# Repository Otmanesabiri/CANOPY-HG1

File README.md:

# Canopy GH-1 — Autonomous Greenhouse Controller

**Canopy GH-1** is an open-hardware, industrial-grade greenhouse climate and irrigation controller powered by the **Raspberry Pi Compute Module 4 (CM4)**. It pairs a deterministic fail-safe control loop and hardware safety interlocks with an embedded **Claude AI agronomic assistant** accessible via web dashboard, REST API, and local voice interface.

---

## Repository Structure

```text
canopy/
├── hw/                         # Custom 4-layer carrier PCB (150 x 100 mm)
│   ├── design.py               # Single-source-of-truth component & netlist DB (186 parts, 162 nets)
│   ├── build_sch.py            # Programmatic KiCad 7/8 schematic generator
│   ├── build_pcb.py            # Programmatic KiCad 7/8 PCB placement & outline generator
│   ├── check_net.py            # Schematic-to-design netlist consistency verifier
│   ├── route_prep.py           # Netclass config & Specctra DSN export for autorouting
│   ├── post_route.py           # SES import, 4-layer copper zone pour, DRC & Gerber/BOM/POS export
│   ├── kicad/                  # KiCad project (canopy.kicad_sch, canopy.kicad_pcb, canopy.dsn, canopy.ses)
│   └── fab/                    # Manufacturing outputs (Gerbers, Excellon drills, BOM, pick-and-place)
├── software/                   # Python 3.11+ asynchronous control daemon & web UI
│   ├── canopy/
│   │   ├── __main__.py         # CLI entry point & daemon runner
│   │   ├── engine.py           # Main async event loop, watchdog heartbeat & subsystem orchestrator
│   │   ├── control.py          # Hysteresis climate, VPD, CO2, lighting & irrigation controller + interlocks
│   │   ├── hal.py              # Hardware abstraction layer (I2C/1-Wire/GPIO drivers + physics simulator)
│   │   ├── radios.py           # LoRa RFM95W sub-GHz telemetry radio driver
│   │   ├── voice.py            # Dual I2S MEMS mic & MAX98357A speaker voice assistant pipeline
│   │   ├── agent.py            # Anthropic Claude tool-calling assistant with setpoint guardrails
│   │   ├── store.py            # SQLite time-series telemetry & event logger
│   │   └── webapp.py           # aiohttp REST API & real-time dark-mode dashboard
│   └── tests/
│       └── test_canopy.py      # 19 unit, safety interlock, 48h simulation & AI tool-calling tests
├── os/                         # Embedded Raspberry Pi OS Bookworm (arm64) customization
│   ├── build-image.sh          # Automated loop-device OS image builder
│   ├── BUILD.md                # Reproducible Docker container build instructions
│   ├── config.txt.append       # Boot config (I2C, SPI, I2S, 1-Wire, hardware watchdog)
│   ├── overlays/               # Device Tree overlay (canopy-gh1-overlay.dts & compiled canopy-gh1.dtbo)
│   └── systemd/                # canopy.service (with WatchdogSec=30s) & canopy-firstboot.service
├── enclosure/                  # Weatherproof 3D-printable enclosure (IP65 gasketed design)
│   ├── canopy_enclosure.scad   # Parametric OpenSCAD source (body, lid, DIN clip, lightpipes)
│   ├── canopy_base.stl         # Enclosure base mesh (and .3mf)
│   └── canopy_lid.stl          # Enclosure lid mesh (and .3mf)
└── docs/                       # Detailed subsystem documentation
    ├── hardware.md             # Schematic, power tree, and PCB layout architecture
    ├── software.md             # Control loop, safety interlocks, and REST API reference
    ├── os-image.md             # OS image build and first-boot provisioning guide
    └── assembly.md             # Mechanical assembly and field wiring instructions
```

---

## Key Features

### 1. Hardware (`canopy/hw`)
- **Compute:** Raspberry Pi Compute Module 4 (CM4) via dual 100-pin Hirose `DF40C-100DS-0.4V` mezzanine connectors.
- **Dual Redundant Power:**
  - **USB-C PD 20V @ 3A (60W)** via `STUSB4500QTR` autonomous USB-PD sink controller (`U1`).
  - **12–24V DC Field Terminal** (`J4`) with ideal-diode/Schottky OR-ing.
  - **High-Efficiency Buck Stages:** `LMR33640ADDAR` (5V @ 4A) + `AP62250WU-7` (3.3V @ 2.5A).
- **Actuation & Switching:**
  - **4x SPDT High-Power Relays (`K1`–`K4`):** Roof vents, exhaust fan, circulation fan, and heater (`ULN2803ADWR` sink driver with `V_FIELD` flyback suppression).
  - **4x 24V Irrigation Solenoid Outputs (`J8`):** Independent zone control with status LEDs.
  - **2x 0–10V / PWM Dimming Outputs:** Supplemental grow lights and variable-speed EC fans.
- **Sensing & Connectivity:**
  - **I2C1 (`J5`):** `SHT31` temperature/humidity, `SCD41` photoacoustic CO2, `PCF8523` RTC with CR1220 backup (`BT1`), and `ADS1115` 16-bit ADC (`U9` — 2x capacitive soil moisture + 2x 0–10V analog inputs with `BAT54S` clamping).
  - **1-Wire (`J6`):** Multi-probe `DS18B20` soil/water temperature sensing.
  - **LoRa Radio (`U6`):** `RFM95W` 868/915 MHz SPI transceiver with u.FL/SMA antenna port (`J10`).
  - **Audio I/O:** Dual `ICS-43434` I2S MEMS microphones (`MK1`, `MK2`) + `MAX98357A` 3.2W Class-D speaker amp (`U7`).
  - **Networking & USB:** Gigabit Ethernet RJ45 with integrated magnetics (`J3`) + dual USB 2.0 Type-A ports (`J2` via `USB2514B-AEZC`).

### 2. Control Software & Safety Engine (`canopy/software`)
- **Deterministic Closed-Loop Control:** Runs independently of cloud connectivity or AI availability.
- **Hardware-Enforced Safety Interlocks:**
  - **Heater / Ventilation Mutual Exclusion:** Never energizes the heater while roof vents or exhaust fans are active.
  - **Thermal Emergency Cutoffs:** Force-off heater above `35 °C`, emergency full ventilation above `40 °C`, emergency frost heating below `5 °C`.
  - **Runaway Irrigation Cutoff:** Hard maximum continuous open time per solenoid valve.
- **Claude AI Assistant Integration:**
  - Supports natural-language diagnostics and guarded setpoint adjustments (`get_status`, `get_history`, `set_target`, `pulse_irrigation`, `set_override`) with strict physical safety boundaries.

---

## Quick Start

### 1. Run the Software Test Suite & Simulator
```powershell
python -m venv .venv
.venv\Scripts\Activate.ps1

pip install -e canopy/software pytest pytest-asyncio pytest-aiohttp tzdata

# Execute all 19 unit, safety interlock & 48h simulation tests
pytest canopy/software/tests/test_canopy.py -v
```

### 2. Launch the Live Simulation Daemon & Web UI
```powershell
python -m canopy --config canopy/os/rootfs/etc/canopy/config.yaml --sim
```
Open **`http://localhost:8080`** in your browser to view the live dashboard, sensor charts, actuator states, and Claude chat interface.

### 3. Hardware Verification & PCB Autorouting Pipeline (Docker)
```powershell
# 1. Verify 100% netlist match between design.py and KiCad schematic
python canopy/hw/check_net.py

# 2. Export Specctra DSN from KiCad 8
docker run --rm -v "${PWD}/canopy:/canopy" kicad/kicad:8.0 python3 /canopy/hw/route_prep.py

# 3. Run headless Freerouting to generate Specctra SES
docker run --rm -v "${PWD}/canopy:/canopy" eclipse-temurin:21-jre `
  java -jar /canopy/hw/lib/freerouting.jar `
  -de /canopy/hw/kicad/canopy.dsn `
  -do /canopy/hw/kicad/canopy.ses `
  --gui.enabled=false --router.max_passes=5

# 4. Import SES, pour 4-layer copper zones, run DRC & export Gerbers/BOM/POS
docker run --rm -v "${PWD}/canopy:/canopy" kicad/kicad:8.0 python3 /canopy/hw/post_route.py --fab
```

### 4. Compile Device Tree Overlay
```powershell
docker run --rm -v "${PWD}/canopy:/canopy" alpine:3.20 sh -c `
  "apk add --no-cache dtc && dtc -@ -I dts -O dtb -o /canopy/os/overlays/canopy-gh1.dtbo /canopy/os/overlays/canopy-gh1-overlay.dts"
```

---

## Verification Status

- **Software Tests:** `19 passed` (`test_canopy.py`) covering hysteresis, safety interlocks, 48-hour physics simulation, REST API, and Claude tool calls.
- **Hardware Netlist:** `186 components`, `162 nets`, `0 mismatches` between `design.py` and `canopy.kicad_sch`.
- **PCB Autorouting:** 5-pass headless Freerouting completed with `0 connection errors` (`canopy.ses`).
- **Device Tree Overlay:** `canopy-gh1.dtbo` compiled cleanly (`1,850 bytes`, 0 warnings).
- **Mechanical Fit:** 150 x 100 mm PCB and 143 x 93 mm M3 mounting hole pattern verified against `canopy_enclosure.scad`.
=======
# Canopy GH-1 greenhouse controller: work in progress (stopped early)

**This package is incomplete. The PCB is placed but NOT routed, and no OS image was built.**

| Item | Where | State |
|---|---|---|
| Design database (parts, MPNs, pin-to-net map) | `hw/design.py` | done; analog values and MPNs are from memory and need datasheet and stock checks |
| Schematic (KiCad 7) + PDF | `hw/kicad/`, `hw/canopy-schematic.pdf` | generated; KiCad's netlist matches the database (186 parts, 162 nets) |
| PCB | `hw/kicad/canopy.kicad_pcb` | placement, outline and planes only. **No tracks**: the autorouter was stopped at pass 8 of 25 with no result |
| Gerbers, drill, pick-and-place, BOM | `hw/fab_UNROUTED_do_not_manufacture/` | exported from the unrouted board. BOM and placement are fine for review; the Gerbers must not be sent to a fab |
| DRC report | `hw/drc_report.txt` | unrouted board: 499 unconnected pads, 359 violations (not yet triaged) |
| Enclosure | `enclosure/` (SCAD, STL, 3MF) | done; meshes watertight; never printed or ingress-tested |
| Software | `software/` | done; 19 tests pass; runs end to end in simulation. Real drivers, voice and the live Claude API call are untested |
| OS image | `os/` | build script, overlay, boot config and units only. The script was never run and nothing was booted |
| Docs | `docs/` | hardware, software, OS image, assembly |

Deviations from the brief: Raspberry Pi CM4 carrier instead of a soldered-down SoC (reasons in `docs/hardware.md`);
Zigbee through an internal USB port for a coordinator stick, not an on-board radio. `docs/hardware.md` section 7
describes the intended layout, not a finished one.

To continue: `cd hw && python3 route_prep.py`, run Freerouting on `kicad/canopy.dsn` to get `kicad/canopy.ses`,
then `python3 post_route.py --fab`. After that, USB and Ethernet pairs and the high-current power path still need
hand rework in KiCad before fabrication. Build the image with `os/build-image.sh` on a Debian/Ubuntu host.

Try the software: `cd software && pip install -e ".[dev]" && pytest`, then `python -m canopy -c cfg.yaml`
with `hardware: {mode: sim}` in the YAML.

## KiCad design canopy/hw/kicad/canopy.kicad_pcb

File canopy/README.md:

# Canopy GH-1 greenhouse controller: work in progress (stopped early)

**This package is incomplete. The PCB is placed but NOT routed, and no OS image was built.**

| Item | Where | State |
|---|---|---|
| Design database (parts, MPNs, pin-to-net map) | `hw/design.py` | done; analog values and MPNs are from memory and need datasheet and stock checks |
| Schematic (KiCad 7) + PDF | `hw/kicad/`, `hw/canopy-schematic.pdf` | generated; KiCad's netlist matches the database (186 parts, 162 nets) |
| PCB | `hw/kicad/canopy.kicad_pcb` | placement, outline and planes only. **No tracks**: the autorouter was stopped at pass 8 of 25 with no result |
| Gerbers, drill, pick-and-place, BOM | `hw/fab_UNROUTED_do_not_manufacture/` | exported from the unrouted board. BOM and placement are fine for review; the Gerbers must not be sent to a fab |
| DRC report | `hw/drc_report.txt` | unrouted board: 499 unconnected pads, 359 violations (not yet triaged) |
| Enclosure | `enclosure/` (SCAD, STL, 3MF) | done; meshes watertight; never printed or ingress-tested |
| Software | `software/` | done; 19 tests pass; runs end to end in simulation. Real drivers, voice and the live Claude API call are untested |
| OS image | `os/` | build script, overlay, boot config and units only. The script was never run and nothing was booted |
| Docs | `docs/` | hardware, software, OS image, assembly |

Deviations from the brief: Raspberry Pi CM4 carrier instead of a soldered-down SoC (reasons in `docs/hardware.md`);
Zigbee through an internal USB port for a coordinator stick, not an on-board radio. `docs/hardware.md` section 7
describes the intended layout, not a finished one.

To continue: `cd hw && python3 route_prep.py`, run Freerouting on `kicad/canopy.dsn` to get `kicad/canopy.ses`,
then `python3 post_route.py --fab`. After that, USB and Ethernet pairs and the high-current power path still need
hand rework in KiCad before fabrication. Build the image with `os/build-image.sh` on a Debian/Ubuntu host.

Try the software: `cd software && pip install -e ".[dev]" && pytest`, then `python -m canopy -c cfg.yaml`
with `hardware: {mode: sim}` in the YAML.

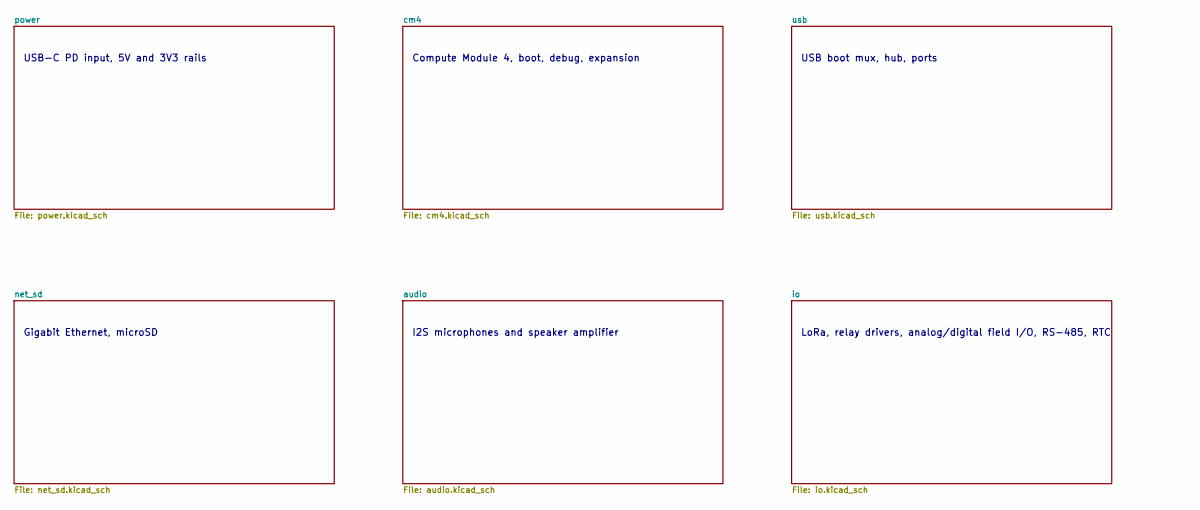
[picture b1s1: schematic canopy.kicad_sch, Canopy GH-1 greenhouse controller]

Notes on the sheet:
USB-C PD input, 5V and 3V3 rails
Compute Module 4, boot, debug, expansion
USB boot mux, hub, ports
Gigabit Ethernet, microSD
I2S microphones and speaker amplifier
LoRa, relay drivers, analog/digital field I/O, RS-485, RTC

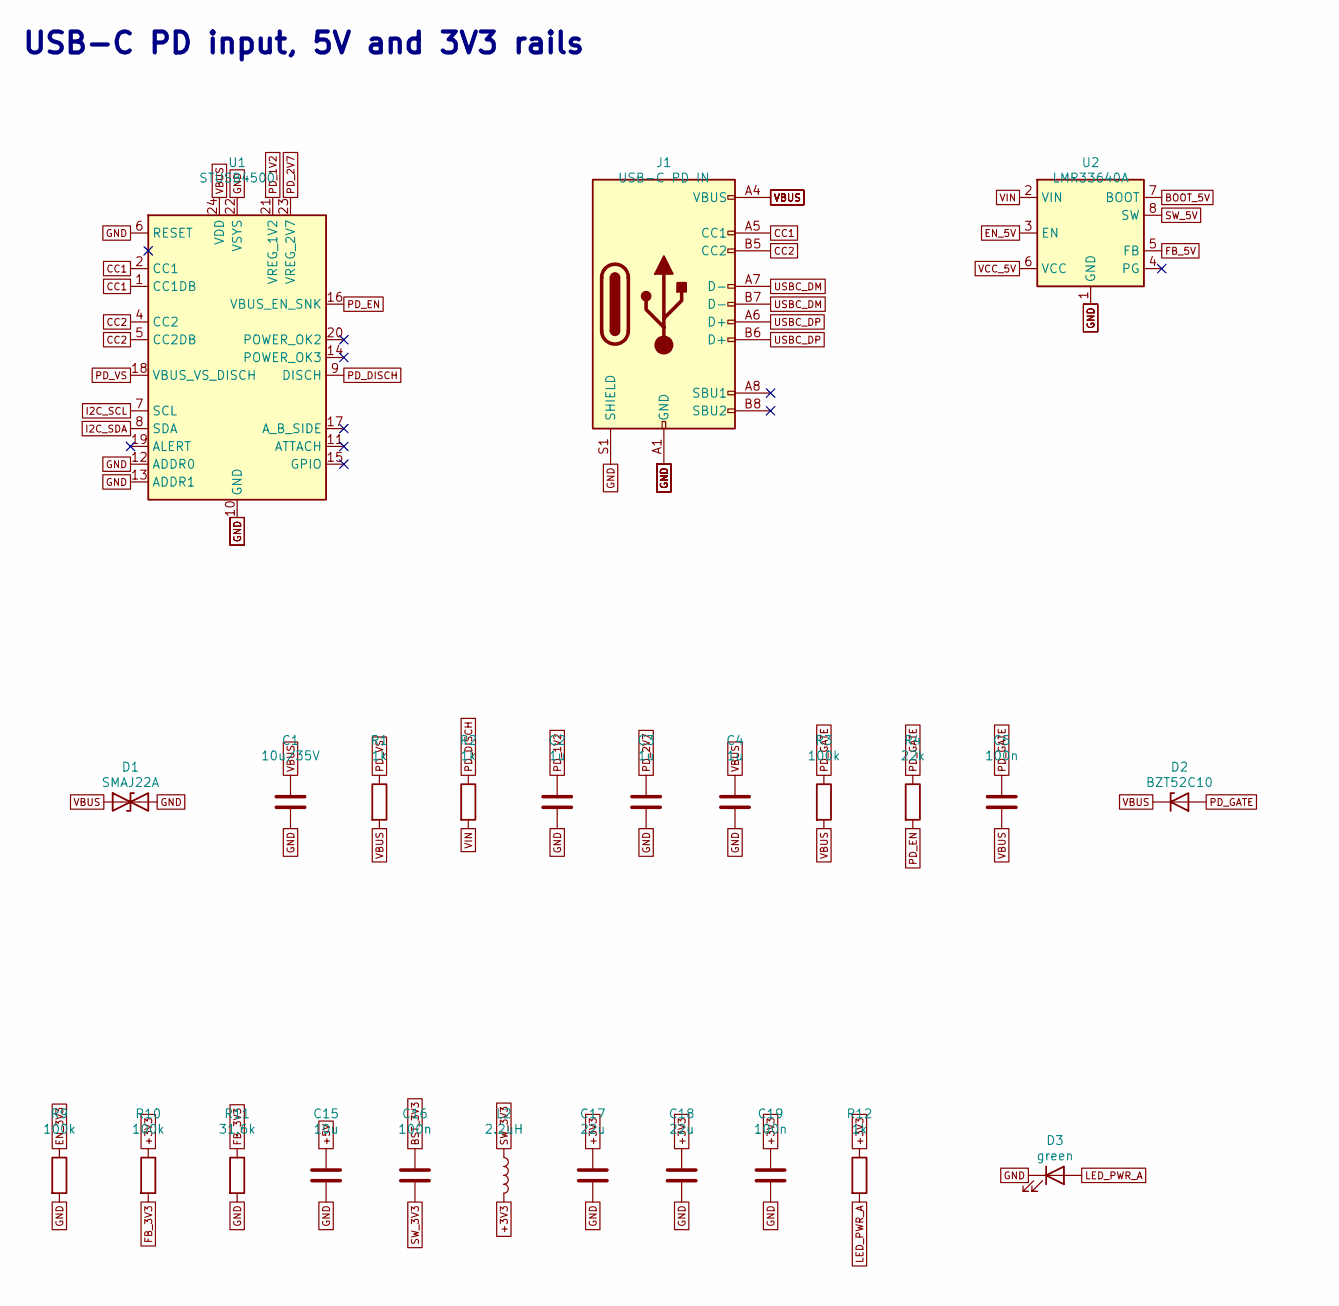
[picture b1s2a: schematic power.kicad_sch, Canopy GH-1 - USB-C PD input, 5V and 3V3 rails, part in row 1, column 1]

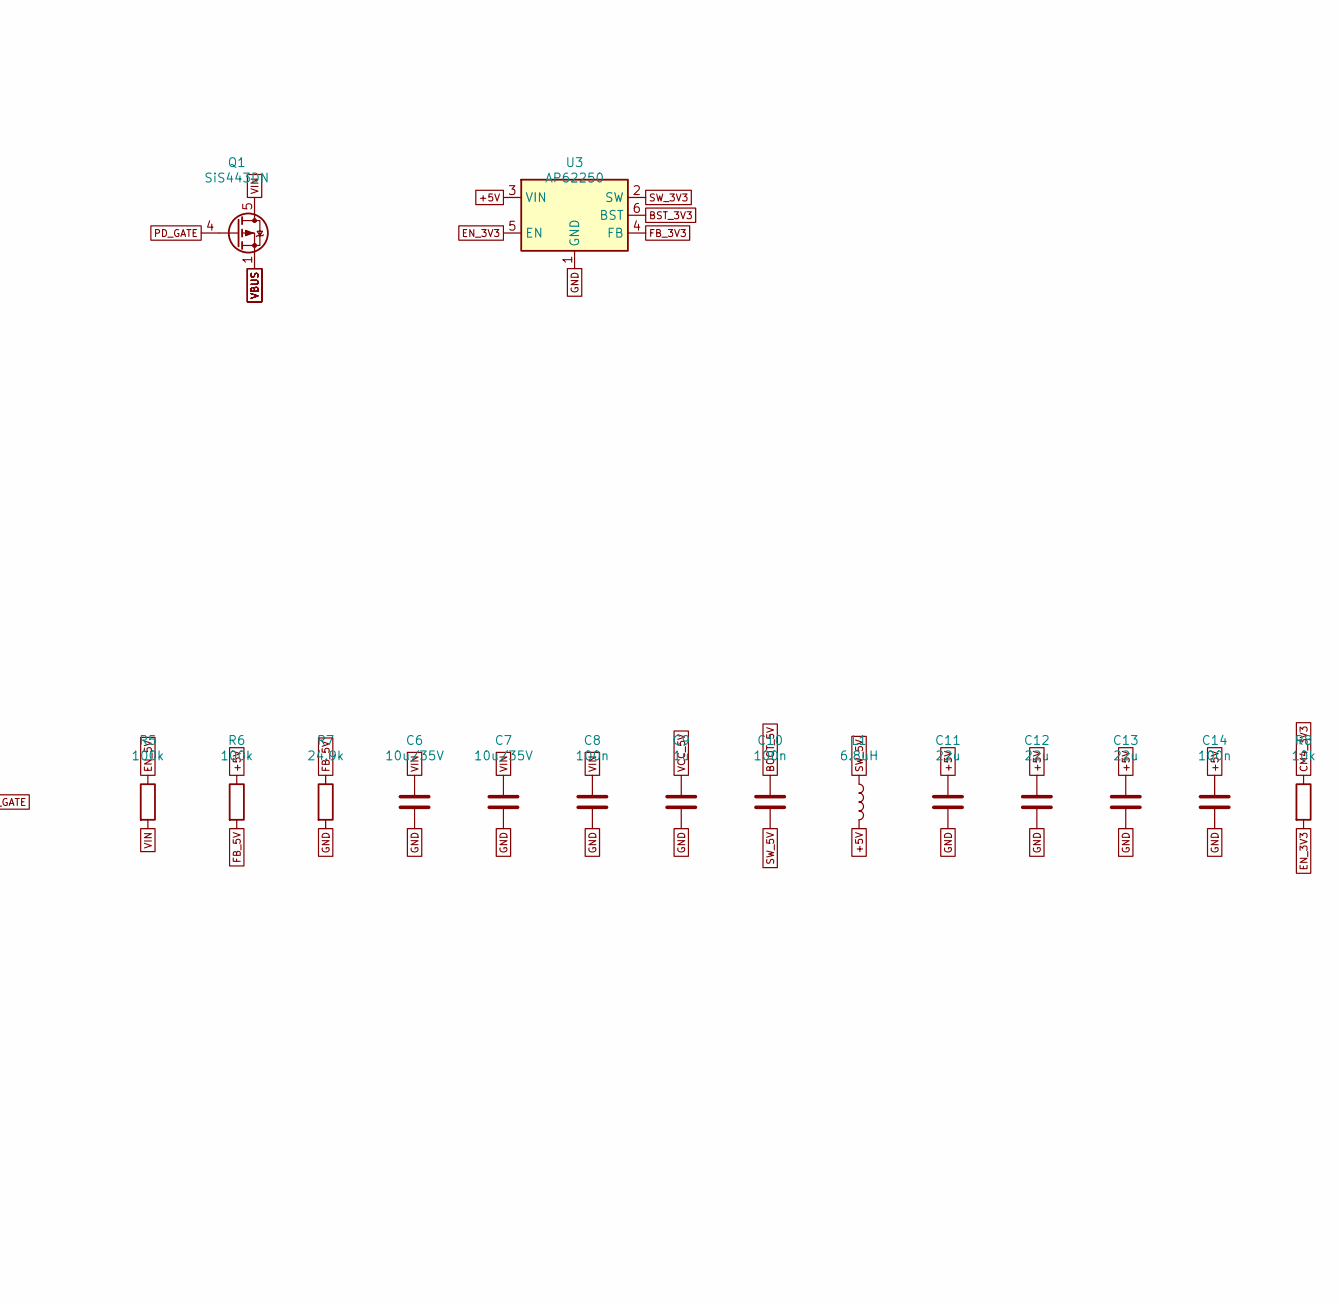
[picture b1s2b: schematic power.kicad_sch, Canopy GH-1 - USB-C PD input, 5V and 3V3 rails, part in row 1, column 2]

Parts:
C1, C6, C7: 10u/35V; C_1206_3216Metric; MPN GRM31CR6YA106KA12L
C2, C3, C4, C9: 1u; C_0603_1608Metric; MPN CL10A105KB8NNNC
C5, C8, C10, C14, C16, C19: 100n; C_0603_1608Metric; MPN GRM188R71H104KA93D
C11, C12, C13, C17, C18: 22u; C_0805_2012Metric; MPN GRM21BR61A226ME44L
C15: 10u; C_0603_1608Metric; MPN GRM188R61A106KE69D
D1: SMAJ22A; D_SMA; MPN SMAJ22A
D2: BZT52C10; D_SOD-123; MPN BZT52C10-7-F
D3: green; LED_0603_1608Metric; MPN LTST-C191KGKT
J1: USB-C PD IN; USB_C_Receptacle_GCT_USB4105-xx-A_16P_TopMnt_Horizontal; MPN USB4105-GF-A
L1: 6.8uH; L_Bourns_SRP7028A_7.3x6.6mm; MPN SRP7028A-6R8M
L2: 2.2uH; L_Coilcraft_XAL4020-XXX; MPN XAL4020-222MEC
Q1: SiS443DN; Vishay_PowerPAK_1212-8_Single; MPN SIS443DN-T1-GE3
R1, R2, R12: 1k; R_0603_1608Metric; MPN RC0603FR-071KL
R3, R5, R6, R9, R10: 100k; R_0603_1608Metric; MPN RC0603FR-07100KL
R4: 22k; R_0603_1608Metric; MPN RC0603FR-0722KL
R7: 24.9k; R_0603_1608Metric; MPN RC0603FR-0724K9L
R8: 10k; R_0603_1608Metric; MPN RC0603FR-0710KL
R11: 31.6k; R_0603_1608Metric; MPN RC0603FR-0731K6L
U1: STUSB4500; QFN-24-1EP_4x4mm_P0.5mm_EP2.7x2.7mm; MPN STUSB4500QTR
U2: LMR33640A; Texas_HSOP-8-1EP_3.9x4.9mm_P1.27mm_ThermalVias; MPN LMR33640ADDAR
U3: AP62250; TSOT-23-6; MPN AP62250WU-7

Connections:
+3V3: C17.1, C18.1, C19.1, L2.2, R10.1, R12.1; also elsewhere on the board
+5V: C11.1, C12.1, C13.1, C14.1, C15.1, L1.2, R6.1, U3.3 (VIN); also elsewhere on the board
BOOT_5V: C10.1, U2.7 (BOOT)
BST_3V3: C16.1, U3.6 (BST)
CC1: J1.A5 (CC1), U1.1 (CC1DB), U1.2 (CC1)
CC2: J1.B5 (CC2), U1.4 (CC2), U1.5 (CC2DB)
CM4_3V3: R8.1; also elsewhere on the board
EN_3V3: R8.2, R9.1, U3.5 (EN)
EN_5V: R5.1, U2.3 (EN)
FB_3V3: R10.2, R11.1, U3.4 (FB)
FB_5V: R6.2, R7.1, U2.5 (FB)
GND: C1.2, C2.2, C3.2, C4.2, C6.2, C7.2, C8.2, C9.2, C11.2, C12.2, C13.2, C14.2, C15.2, C17.2, C18.2, C19.2, D1.2 (A2), D3.1 (K), J1.A1 (GND), J1.A12 (GND), J1.B1 (GND), J1.B12 (GND), J1.S1 (SHIELD), R7.2, R9.2, R11.2, U1.6 (RESET), U1.10 (GND), U1.12 (ADDR0), U1.13 (ADDR1), U1.22 (VSYS), U1.25 (GND), U2.1 (GND), U2.9 (GND), U3.1 (GND); also elsewhere on the board
I2C_SCL: U1.7 (SCL); also elsewhere on the board
I2C_SDA: U1.8 (SDA); also elsewhere on the board
LED_PWR_A: D3.2 (A), R12.2
PD_1V2: C2.1, U1.21 (VREG_1V2)
PD_2V7: C3.1, U1.23 (VREG_2V7)
PD_DISCH: R2.1, U1.9 (DISCH)
PD_EN: R4.2, U1.16 (VBUS_EN_SNK)
PD_GATE: C5.1, D2.2 (A), Q1.4 (G), R3.1, R4.1
PD_VS: R1.1, U1.18 (VBUS_VS_DISCH)
SW_3V3: C16.2, L2.1, U3.2 (SW)
SW_5V: C10.2, L1.1, U2.8 (SW)
USBC_DM: J1.A7 (D-), J1.B7 (D-); also elsewhere on the board
USBC_DP: J1.A6 (D+), J1.B6 (D+); also elsewhere on the board
VBUS: C1.1, C4.1, C5.2, D1.1 (A1), D2.1 (K), J1.A4 (VBUS), J1.A9 (VBUS), J1.B4 (VBUS), J1.B9 (VBUS), Q1.1 (S), Q1.2 (S), Q1.3 (S), R1.2, R3.2, U1.24 (VDD)
VCC_5V: C9.1, U2.6 (VCC)
VIN: C6.1, C7.1, C8.1, Q1.5 (D), R2.2, R5.2, U2.2 (VIN)

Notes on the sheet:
USB-C PD input, 5V and 3V3 rails

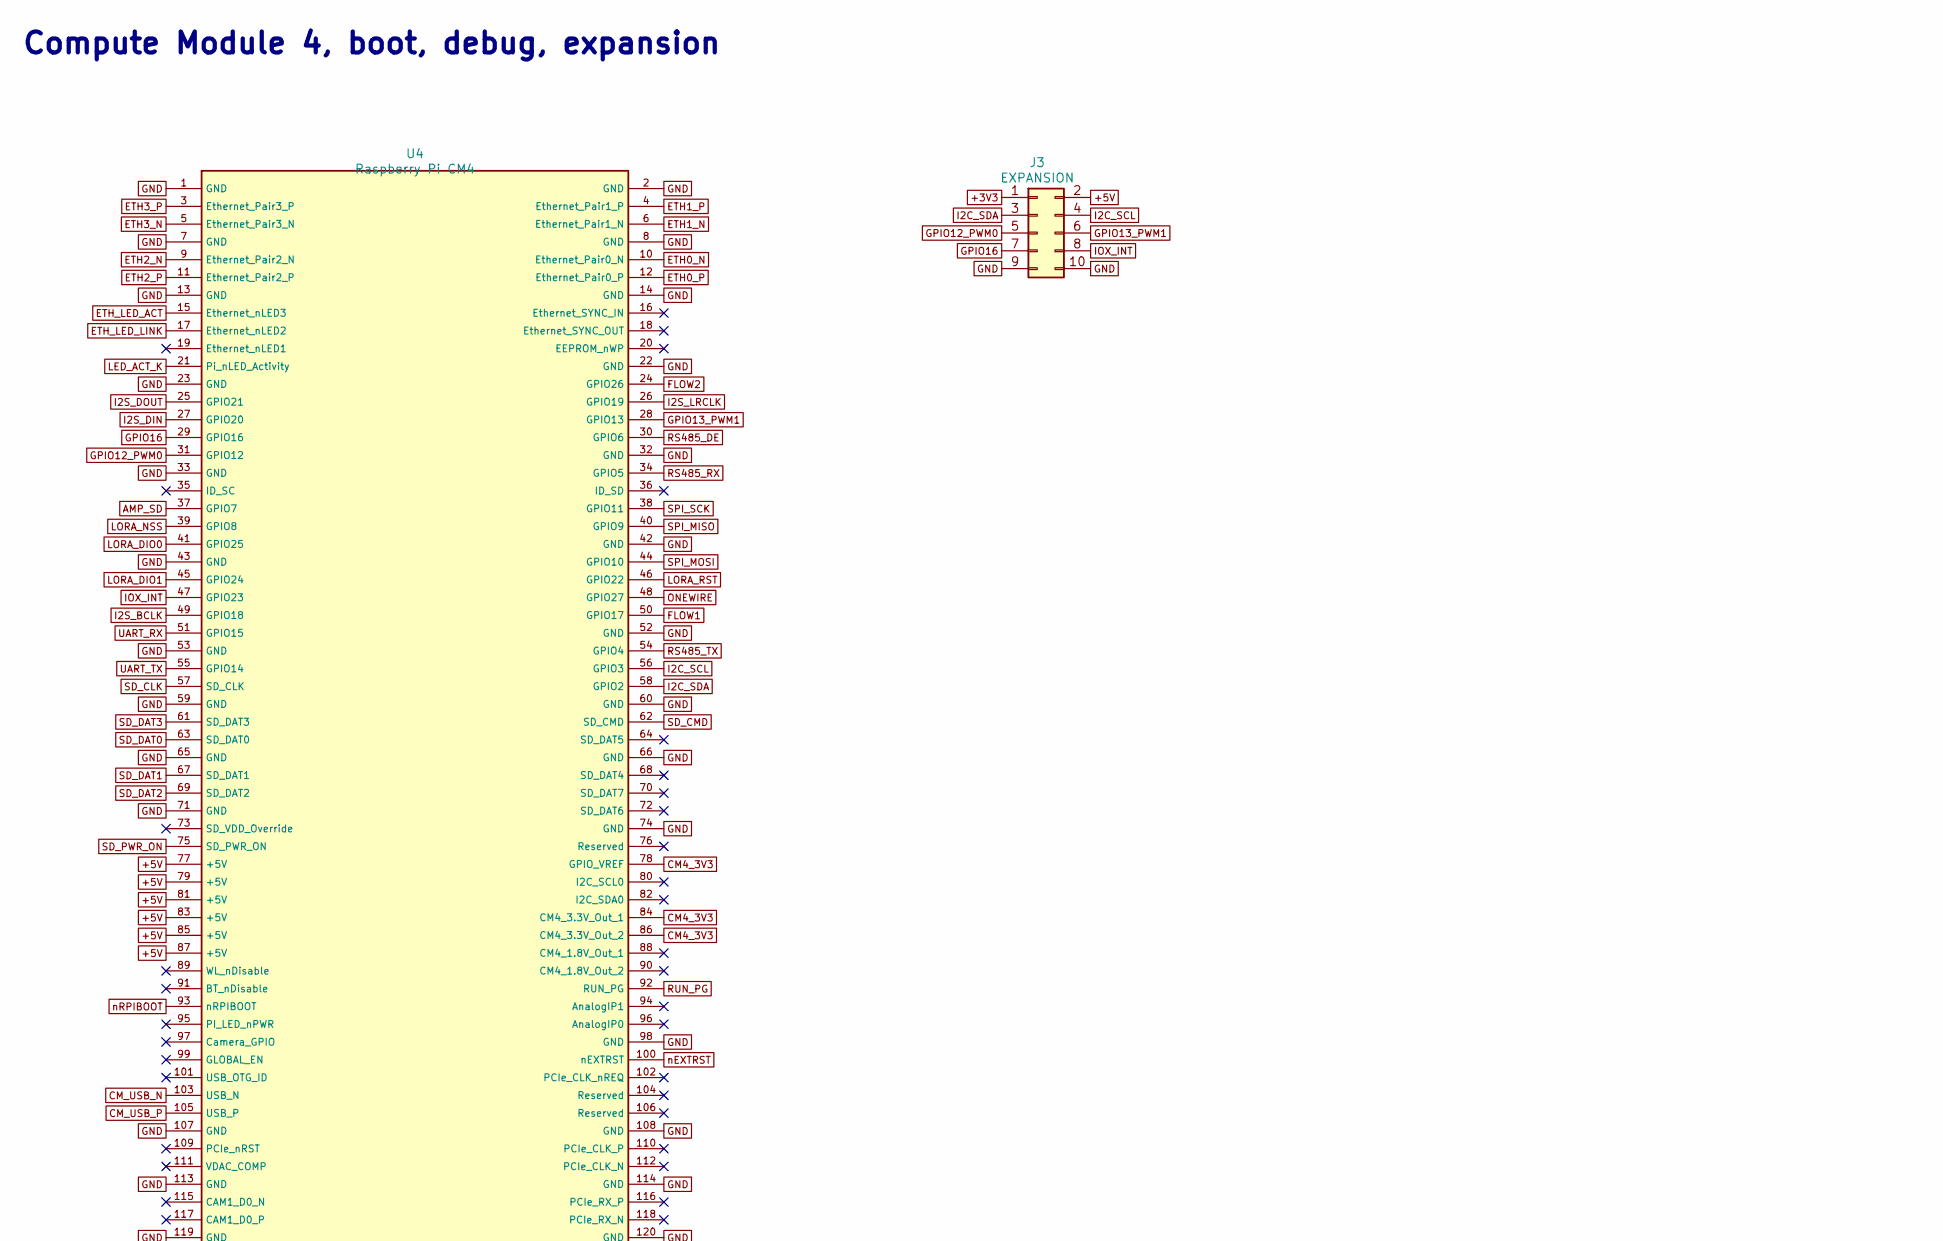
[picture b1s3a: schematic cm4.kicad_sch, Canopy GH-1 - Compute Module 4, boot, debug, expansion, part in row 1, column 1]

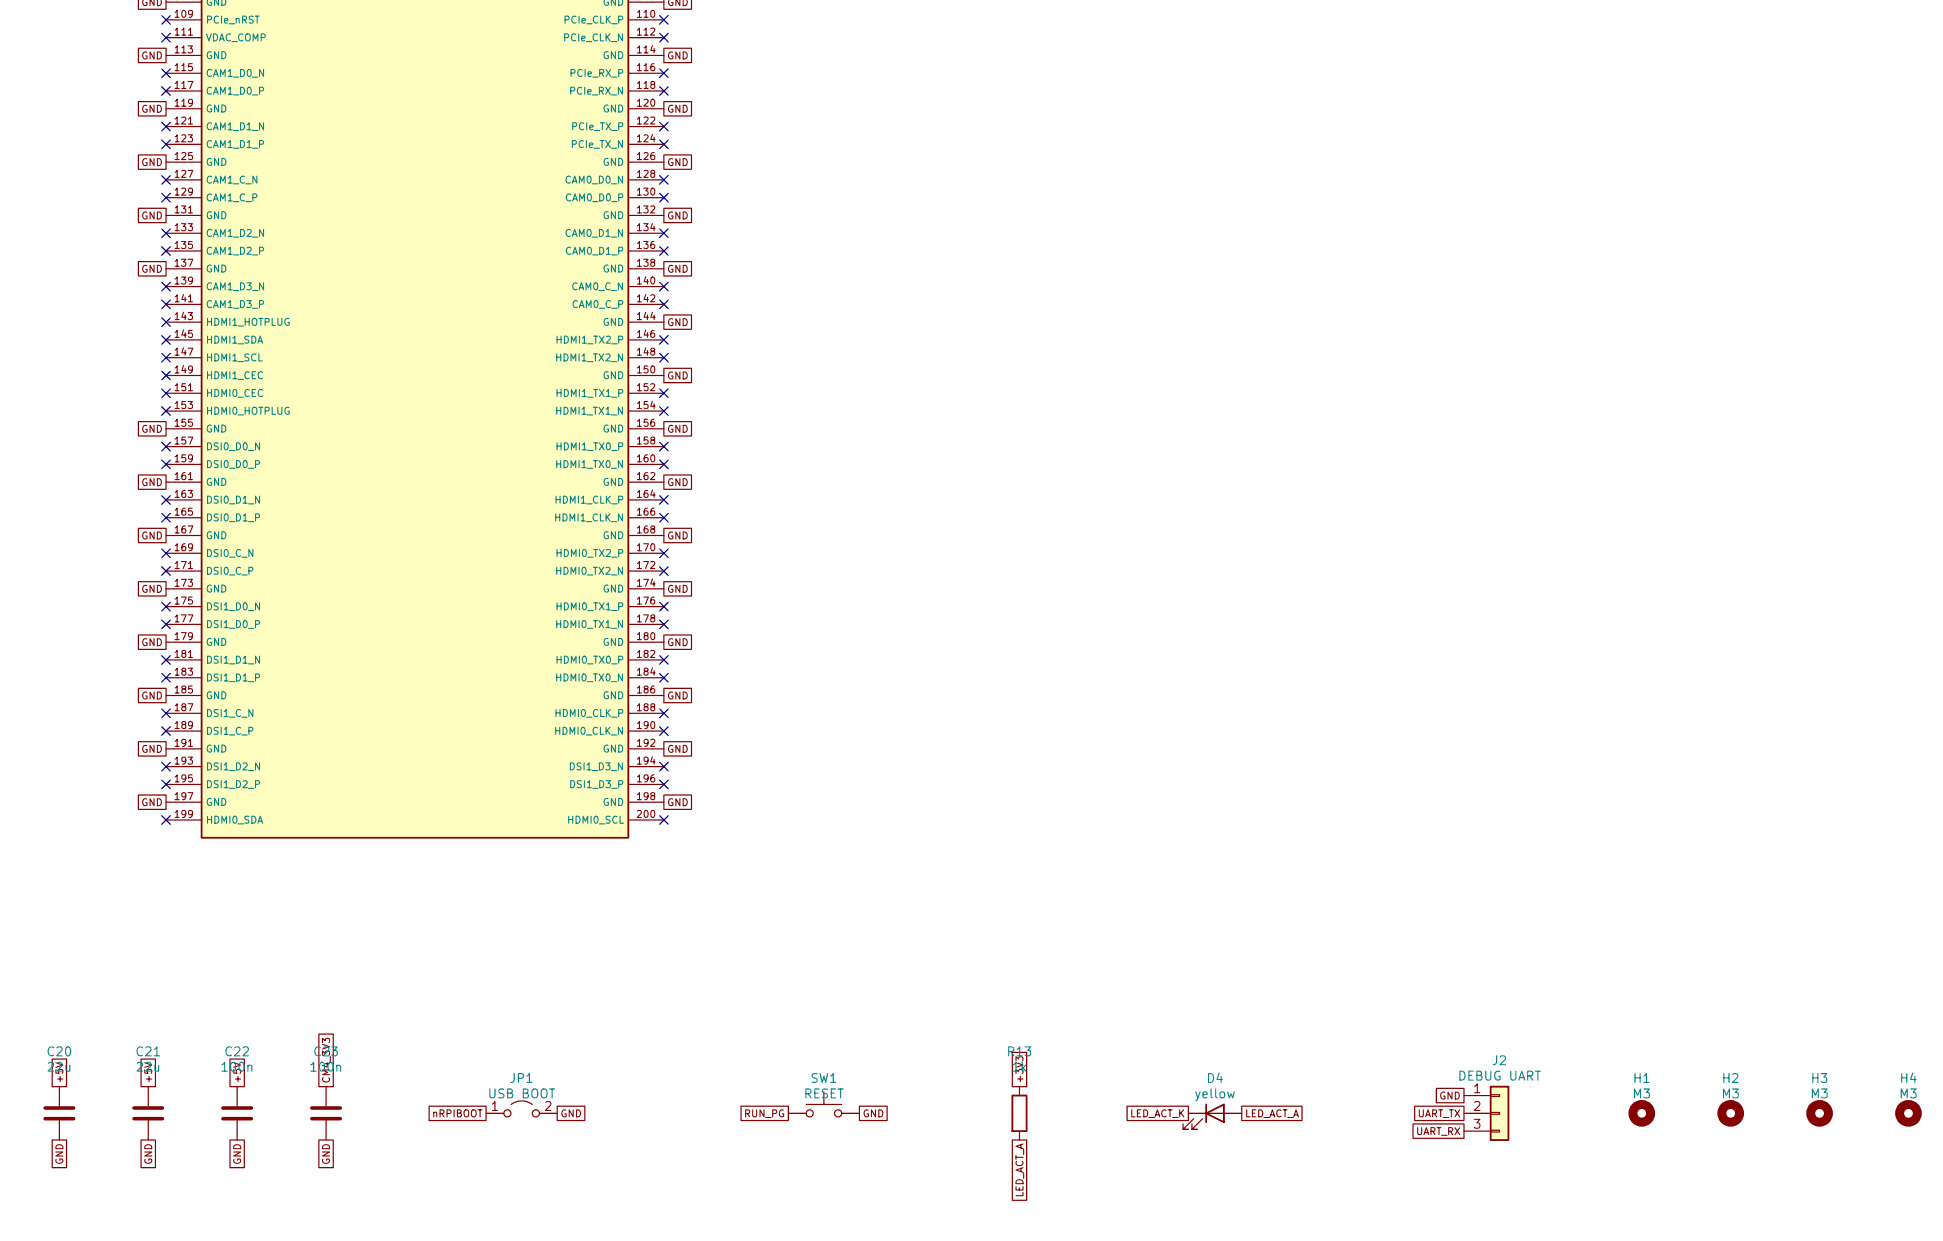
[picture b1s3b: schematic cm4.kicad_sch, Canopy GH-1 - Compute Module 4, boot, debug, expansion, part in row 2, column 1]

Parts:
C20, C21: 22u; C_0805_2012Metric; MPN GRM21BR61A226ME44L
C22, C23: 100n; C_0603_1608Metric; MPN GRM188R71H104KA93D
D4: yellow; LED_0603_1608Metric; MPN LTST-C191KSKT
H1, H2, H3, H4: M3; MountingHole_3.2mm_M3
J2: DEBUG UART; PinHeader_1x03_P2.54mm_Vertical; MPN M20-9990345
J3: EXPANSION; PinHeader_2x05_P2.54mm_Vertical; MPN M20-9980545
JP1: USB BOOT; PinHeader_1x02_P2.54mm_Vertical; MPN M20-9990245
R13: 1k; R_0603_1608Metric; MPN RC0603FR-071KL
SW1: RESET; SW_SPST_B3U-1000P; MPN B3U-1000P
U4: Raspberry Pi CM4; Raspberry-Pi-4-Compute-Module; MPN CM4102000 (2GB, Wi-Fi/BT, Lite) or CM41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

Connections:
+3V3: J3.1, R13.1; also elsewhere on the board
+5V: C20.1, C21.1, C22.1, J3.2, U4.77 (+5V), U4.79 (+5V), U4.81 (+5V), U4.83 (+5V), U4.85 (+5V), U4.87 (+5V); also elsewhere on the board
AMP_SD: U4.37 (GPIO7); also elsewhere on the board
CM4_3V3: C23.1, U4.78 (GPIO_VREF), U4.84 (CM4_3.3V_Out_1), U4.86 (CM4_3.3V_Out_2); also elsewhere on the board
CM_USB_N: U4.103 (USB_N); also elsewhere on the board
CM_USB_P: U4.105 (USB_P); also elsewhere on the board
ETH0_N: U4.10 (Ethernet_Pair0_N); also elsewhere on the board
ETH0_P: U4.12 (Ethernet_Pair0_P); also elsewhere on the board
ETH1_N: U4.6 (Ethernet_Pair1_N); also elsewhere on the board
ETH1_P: U4.4 (Ethernet_Pair1_P); also elsewhere on the board
ETH2_N: U4.9 (Ethernet_Pair2_N); also elsewhere on the board
ETH2_P: U4.11 (Ethernet_Pair2_P); also elsewhere on the board
ETH3_N: U4.5 (Ethernet_Pair3_N); also elsewhere on the board
ETH3_P: U4.3 (Ethernet_Pair3_P); also elsewhere on the board
ETH_LED_ACT: U4.15 (Ethernet_nLED3); also elsewhere on the board
ETH_LED_LINK: U4.17 (Ethernet_nLED2); also elsewhere on the board
FLOW1: U4.50 (GPIO17); also elsewhere on the board
FLOW2: U4.24 (GPIO26); also elsewhere on the board
GND: C20.2, C21.2, C22.2, C23.2, J2.1, J3.9, J3.10, JP1.2 (B), SW1.2, U4.1 (GND), U4.2 (GND), U4.7 (GND), U4.8 (GND), U4.13 (GND), U4.14 (GND), U4.22 (GND), U4.23 (GND), U4.32 (GND), U4.33 (GND), U4.42 (GND), U4.43 (GND), U4.52 (GND), U4.53 (GND), U4.59 (GND), U4.60 (GND), U4.65 (GND), U4.66 (GND), U4.71 (GND), U4.74 (GND), U4.98 (GND), U4.107 (GND), U4.108 (GND), U4.113 (GND), U4.114 (GND), U4.119 (GND), U4.120 (GND), U4.125 (GND), U4.126 (GND), U4.131 (GND), U4.132 (GND), U4.137 (GND), U4.138 (GND), U4.144 (GND), U4.150 (GND), U4.155 (GND), U4.156 (GND), U4.161 (GND), U4.162 (GND), U4.167 (GND), U4.168 (GND), U4.173 (GND), U4.174 (GND), U4.179 (GND), U4.180 (GND), U4.185 (GND), U4.186 (GND), U4.191 (GND), U4.192 (GND), U4.197 (GND), U4.198 (GND); also elsewhere on the board
GPIO12_PWM0: J3.5, U4.31 (GPIO12)
GPIO13_PWM1: J3.6, U4.28 (GPIO13)
GPIO16: J3.7, U4.29 (GPIO16)
I2C_SCL: J3.4, U4.56 (GPIO3); also elsewhere on the board
I2C_SDA: J3.3, U4.58 (GPIO2); also elsewhere on the board
I2S_BCLK: U4.49 (GPIO18); also elsewhere on the board
I2S_DIN: U4.27 (GPIO20); also elsewhere on the board
I2S_DOUT: U4.25 (GPIO21); also elsewhere on the board
I2S_LRCLK: U4.26 (GPIO19); also elsewhere on the board
IOX_INT: J3.8, U4.47 (GPIO23); also elsewhere on the board
LED_ACT_A: D4.2 (A), R13.2
LED_ACT_K: D4.1 (K), U4.21 (Pi_nLED_Activity)
LORA_DIO0: U4.41 (GPIO25); also elsewhere on the board
LORA_DIO1: U4.45 (GPIO24); also elsewhere on the board
LORA_NSS: U4.39 (GPIO8); also elsewhere on the board
LORA_RST: U4.46 (GPIO22); also elsewhere on the board
ONEWIRE: U4.48 (GPIO27); also elsewhere on the board
RS485_DE: U4.30 (GPIO6); also elsewhere on the board
RS485_RX: U4.34 (GPIO5); also elsewhere on the board
RS485_TX: U4.54 (GPIO4); also elsewhere on the board
RUN_PG: SW1.1, U4.92 (RUN_PG)
SD_CLK: U4.57 (SD_CLK); also elsewhere on the board
SD_CMD: U4.62 (SD_CMD); also elsewhere on the board
SD_DAT0: U4.63 (SD_DAT0); also elsewhere on the board
SD_DAT1: U4.67 (SD_DAT1); also elsewhere on the board
SD_DAT2: U4.69 (SD_DAT2); also elsewhere on the board
SD_DAT3: U4.61 (SD_DAT3); also elsewhere on the board
SD_PWR_ON: U4.75 (SD_PWR_ON); also elsewhere on the board
SPI_MISO: U4.40 (GPIO9); also elsewhere on the board
SPI_MOSI: U4.44 (GPIO10); also elsewhere on the board
SPI_SCK: U4.38 (GPIO11); also elsewhere on the board
UART_RX: J2.3, U4.51 (GPIO15)
UART_TX: J2.2, U4.55 (GPIO14)
nEXTRST: U4.100 (nEXTRST); also elsewhere on the board
nRPIBOOT: JP1.1 (A), U4.93 (nRPIBOOT); also elsewhere on the board

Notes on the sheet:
Compute Module 4, boot, debug, expansion
